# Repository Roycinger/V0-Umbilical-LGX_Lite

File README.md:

# V0-Umbilical-LGX_Lite
 
### Toolhead PCB BOM
| Part      | Quantity | Notes | Digikey Part Number | Link |
| ----------- | :-: | ----------- | ----------- |----------- |
| 16 Pin Socket (Right Angle)   | 1 |  Molex 1053141316  | WM15165-ND   | https://www.digikey.com/en/products/detail/molex/1053141216/6164254?s=N4IgTCBcDaIIwAYCsBmOAWOY4DYQF0BfIA |
| 2 pin JST XH    | 6 |  B2B-XH  | 455-2273-ND   | https://www.digikey.com/en/products/detail/jst-sales-america-inc/B2B-XH-AM-LF-SN/1016630 |
| 3 pin JST XH    | 1 |  B3B-XH  | 455-2248-ND   | https://www.digikey.com/en/products/detail/jst-sales-america-inc/B3B-XH-A-LF-SN/1651046 |
| 4 pin JST XH    | 1 |  B4B-XH  | 455-2249-ND   | https://www.digikey.com/en/products/detail/jst-sales-america-inc/B4B-XH-A-LF-SN/1651047 |

### Frame PCB BOM
| Part      | Quantity | Notes | Digikey Part Number | Link |
| ----------- | :-: | ----------- | ----------- |----------- |
| 16 Pin Socket   |  1 | MOLEX 1053101216 | WM15060-ND   | https://www.digikey.com/en/products/detail/molex/1053101216/6164149?s=N4IgTCBcDaIIwAYCsBmRcxwGwgLoF8g |
| SMD Thermistor  |  1 | 100K 0805 Thermistor | BC2562CT-ND   | https://www.digikey.com/en/products/detail/vishay-beyschlag-draloric-bc-components/NTCS0805E3104FXT/2237371 |
| 2 pin JST XH    |  5 | 2.5mm pitch | 455-2273-ND   | https://www.digikey.com/en/products/detail/jst-sales-america-inc/B2B-XH-AM-LF-SN/1016630 |
| 3 pin JST XH    |  3 | 2.5mm pitch | 455-2248-ND   | https://www.digikey.com/en/products/detail/jst-sales-america-inc/B3B-XH-A-LF-SN/1651046 |
| 4 pin JST XH    |  3 | 2.5mm pitch | 455-2249-ND   | https://www.digikey.com/en/products/detail/jst-sales-america-inc/B4B-XH-A-LF-SN/1651047 |
| Screw Terminal  |  1 | 5.08mm pitch | 277-1247-ND     | https://www.digikey.com/en/products/detail/phoenix-contact/1729128/260615 |

### Optional Parts
| Part      | Quantity | Notes | Digikey Part Number | Link |
| ----------- | :-: | ----------- | ----------- |----------- |
| 0805 10uF Capacitor  |  3 | Not required for Neopixel Strips | 1276-2399-1-ND   | https://www.digikey.com/en/products/detail/samsung-electro-mechanics/CL21A106KOCLRNC/3888057 |

### Cable BOM
| Part      | Quantity | Notes | Digikey Part Number | Link |
| ----------- | :-: | ----------- | ----------- |----------- |
| 16 pin Plug  |  2 | Molex 1053081216 | WM15025-ND   | https://www.digikey.de/de/products/detail/molex/1053081216/6164114?s=N4IgTCBcDaIIwAYCsBmBAOOY4DYQF0BfIA |
| Nanofit Crimp  |  32 | Molex 1053002200 | WM14957CT-ND   | https://www.digikey.de/de/products/detail/molex/1053002200/6131599 |
| 20AWG Wire  |  16 | 200-220mm sections. Smaller wire (i.e.24AWG can be used. Make sure to user proper wire size for heater and ground wires |    |  |

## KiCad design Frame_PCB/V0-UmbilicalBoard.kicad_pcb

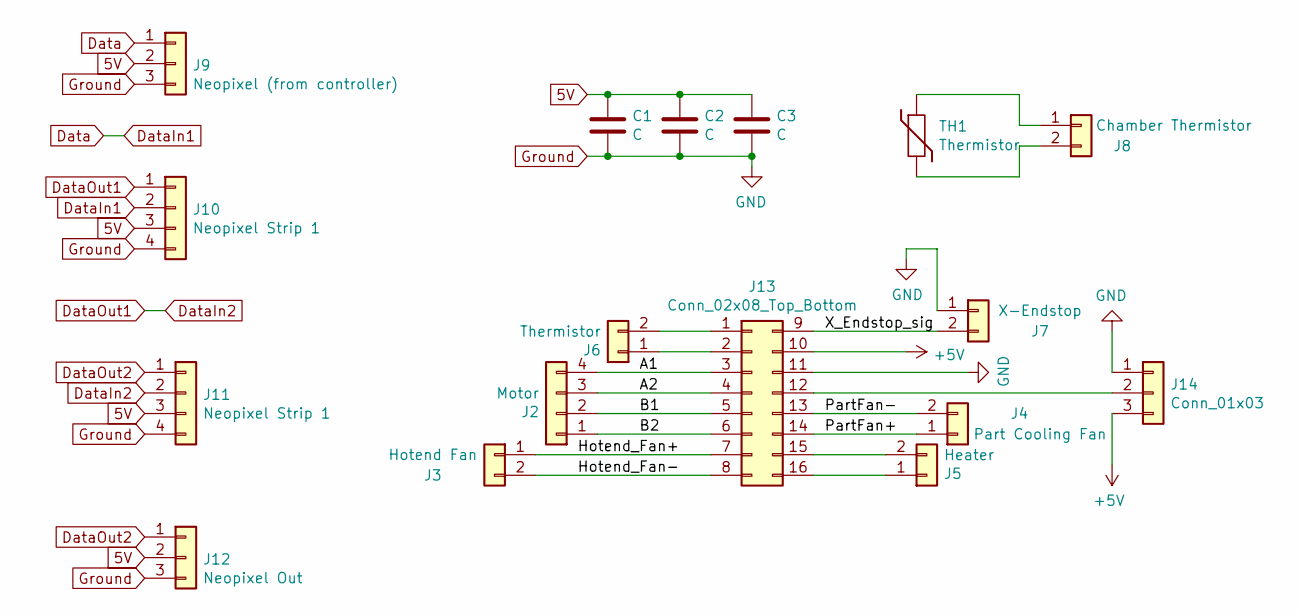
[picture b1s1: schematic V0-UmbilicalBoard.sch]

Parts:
C1, C2, C3: C; C_0805_2012Metric_Pad1.18x1.45mm_HandSolder
J2: Motor; JST_XH_B4B-XH-A_1x04_P2.50mm_Vertical
J3: Hotend Fan; JST_XH_B2B-XH-A_1x02_P2.50mm_Vertical
J4: Part Cooling Fan; JST_XH_B2B-XH-A_1x02_P2.50mm_Vertical
J5: Heater; TerminalBlock_Phoenix_MKDS-1,5-2-5.08_1x02_P5.08mm_Horizont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
J6: Thermistor; JST_XH_B2B-XH-A_1x02_P2.50mm_Vertical
J7: X-Endstop; JST_XH_B2B-XH-A_1x02_P2.50mm_Vertical
J8: Chamber Thermistor; JST_XH_B2B-XH-A_1x02_P2.50mm_Vertical
J9: Neopixel (from controller); JST_XH_B3B-XH-A_1x03_P2.50mm_Vertical
J10, J11: Neopixel Strip 1; JST_XH_B4B-XH-A_1x04_P2.50mm_Vertical
J12: Neopixel Out; JST_XH_B3B-XH-A_1x03_P2.50mm_Vertical
J13: Conn_02x08_Top_Bottom; Molex_Nano-Fit_105310-xx16_2x08_P2.50mm_Vertical
J14: Conn_01x03; JST_XH_B3B-XH-A_1x03_P2.50mm_Vertical
TH1: Thermistor; R_0805_2012Metric_Pad1.20x1.40mm_HandSolder

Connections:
5V: C1.1, C2.1, C3.1, J9.2, J10.3, J11.3, J12.2
+5V: J13.10, J14.3; also elsewhere on the board
/A1: J2.4, J13.3
/A2: J2.3, J13.4
/B1: J2.2, J13.5
/B2: J2.1, J13.6
/Hotend_Fan+: J3.1, J13.7
/Hotend_Fan-: J3.2, J13.8
/KlickySignal: J13.12, J14.2; also elsewhere on the board
/PartFan+: J4.1, J13.14
/PartFan-: J4.2, J13.13
/X_Endstop_sig: J7.2, J13.9
Data: J9.1, J10.2
DataIn2: J10.1, J11.2
DataOut2: J11.1, J12.1
Ground: C1.2, C2.2, C3.2, J7.1, J9.3, J10.4, J11.4, J12.3, J13.11, J14.1; also elsewhere on the board
unnamed: J8.1, TH1.1
unnamed: J8.2, TH1.2
unnamed: J6.2, J13.1
unnamed: J6.1, J13.2
unnamed: J5.2, J13.15
unnamed: J5.1, J13.16

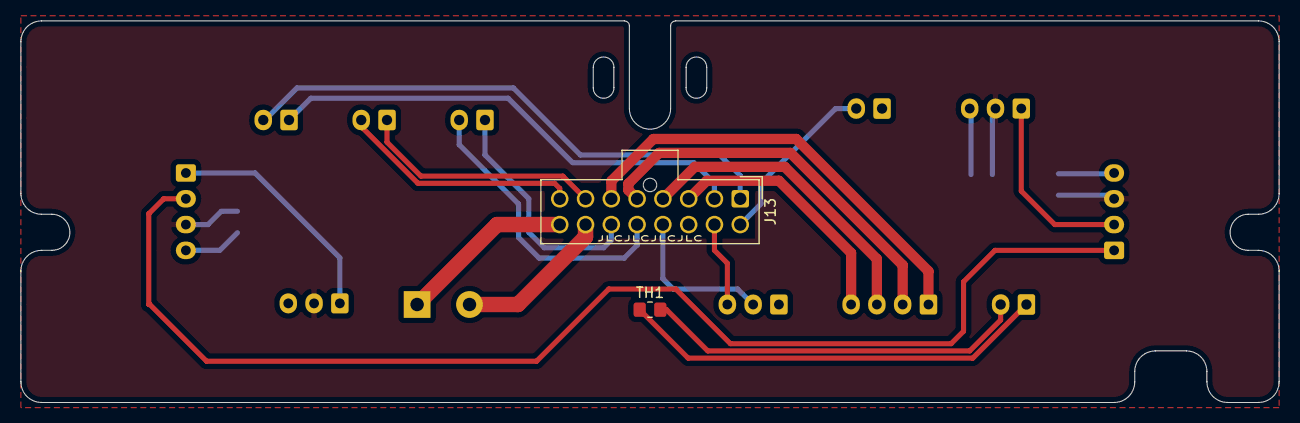
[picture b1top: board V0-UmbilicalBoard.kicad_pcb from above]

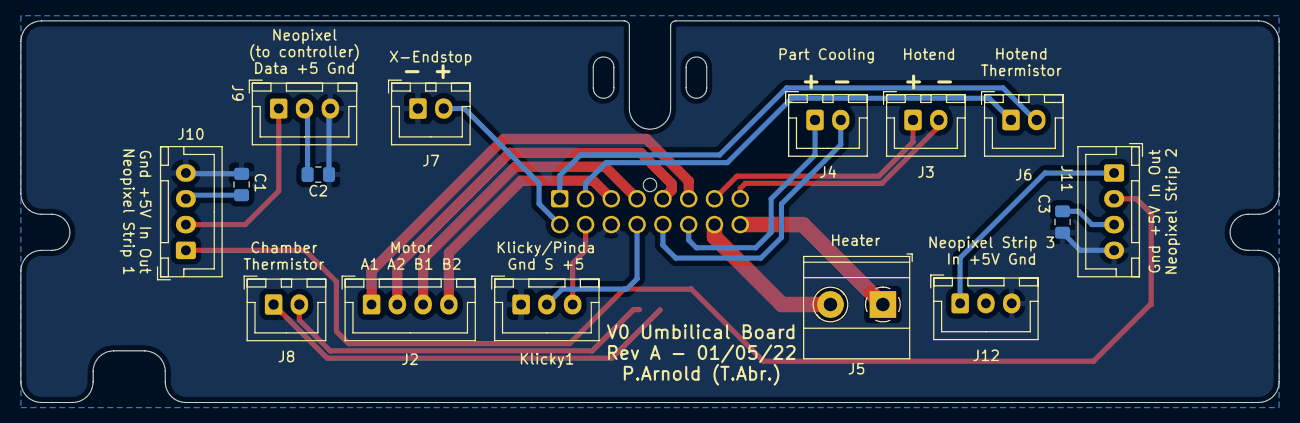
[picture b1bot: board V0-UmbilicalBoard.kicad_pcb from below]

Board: 2 copper layers, 122.0 x 37.0 mm, 17 parts (15 on the bottom side), 22 nets.

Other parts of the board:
Klicky1: Conn_01x03; JST_XH_B3B-XH-A_1x03_P2.50mm_Vertical

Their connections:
+5V: Klicky1.3; also elsewhere on the board
/KlickySignal: Klicky1.2; also elsewhere on the board
Ground: Klicky1.1; also elsewhere on the board

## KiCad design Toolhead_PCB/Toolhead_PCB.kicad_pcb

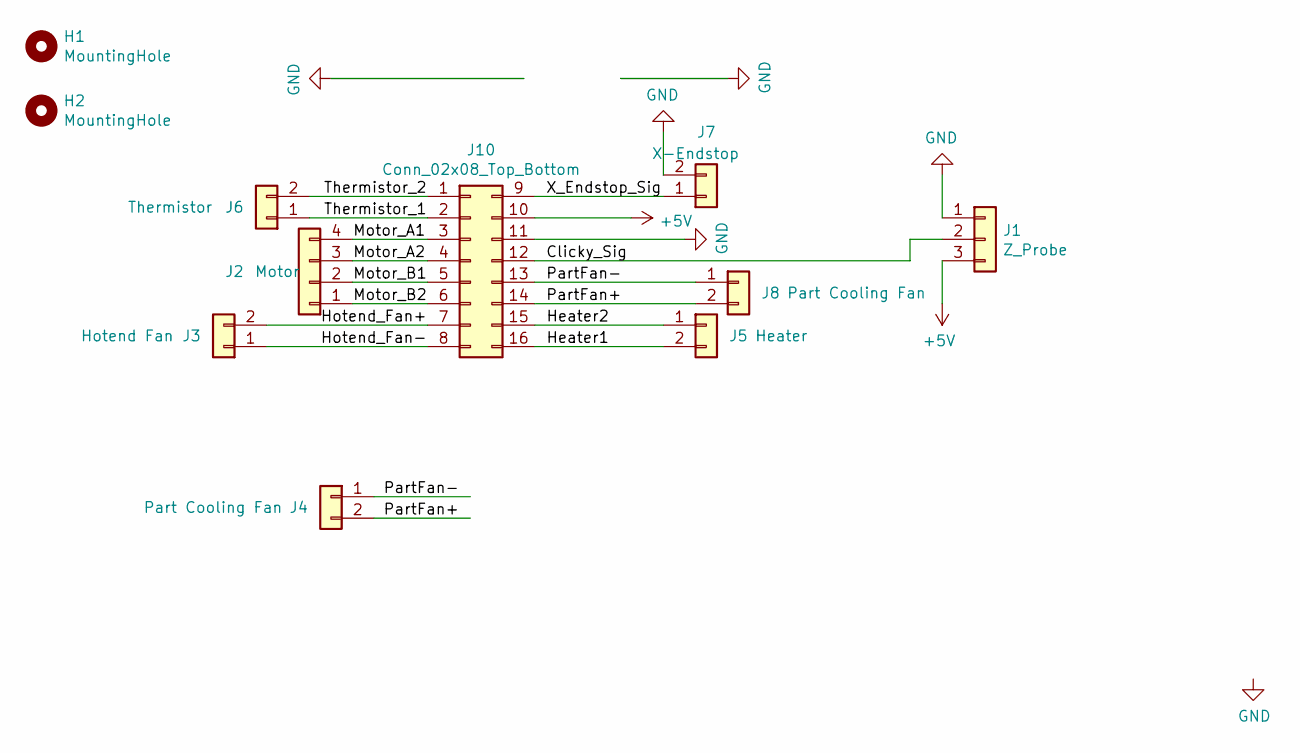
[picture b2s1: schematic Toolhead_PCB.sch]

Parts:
H1, H2: MountingHole; MountingHole_3.2mm_M3
J1: Z_Probe; JST_XH_B3B-XH-A_1x03_P2.50mm_Vertical
J2: Motor; JST_XH_B4B-XH-A_1x04_P2.50mm_Vertical
J3: Hotend Fan; JST_XH_B2B-XH-A_1x02_P2.50mm_Vertical
J4, J8: Part Cooling Fan; JST_XH_B2B-XH-A_1x02_P2.50mm_Vertical
J5: Heater; JST_XH_B2B-XH-A_1x02_P2.50mm_Vertical
J6: Thermistor; JST_XH_B2B-XH-A_1x02_P2.50mm_Vertical
J7: X-Endstop; JST_XH_B2B-XH-A_1x02_P2.50mm_Vertical
J10: Conn_02x08_Top_Bottom; Molex_Nano-Fit_105314-xx16_2x08_P2.50mm_Horizontal

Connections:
+5V: J1.3, J10.10
/Clicky_Sig: J1.2, J10.12
/Heater1: J5.2, J10.16
/Heater2: J5.1, J10.15
/Hotend_Fan+: J3.2, J10.7
/Hotend_Fan-: J3.1, J10.8
/Motor_A1: J2.4, J10.3
/Motor_A2: J2.3, J10.4
/Motor_B1: J2.2, J10.5
/Motor_B2: J2.1, J10.6
/PartFan+: J4.2, J8.2, J10.14
/PartFan-: J4.1, J8.1, J10.13
/Thermistor_1: J6.1, J10.2
/Thermistor_2: J6.2, J10.1
/X_Endstop_Sig: J7.1, J10.9
GND: J1.1, J7.2, J10.11

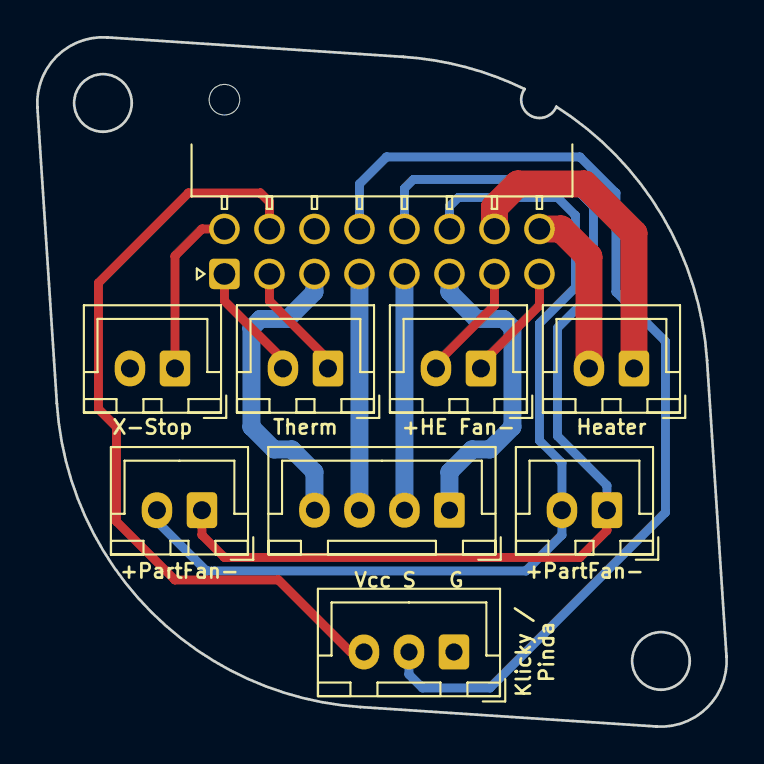
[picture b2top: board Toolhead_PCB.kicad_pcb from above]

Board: 2 copper layers, 38.3 x 38.3 mm, 11 parts (0 on the bottom side), 16 nets.

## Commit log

2022-01-05 Some adjustments
2022-02-05 changed hotend fan silkscreen lettering
    + and - were swapped unintentionally
2022-02-05 minor schematic correction
    renamed wire label "Clicky_Sig" to "Klicky_Sig" on the Toolhead PCB
2022-03-02 uploaded STLs
    STLs for toolhead spacers and frame PCB cover.
    FramePCBCover_topHole.stl features a hole in the cover to solder a 3-pin JST-XH on the opposite side for routing a servo cable to the print chamber (i.e. nozzle wiper arm mechanism)
